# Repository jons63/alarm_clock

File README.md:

# Alarm clock with mp3 song support
This project spawned when my sister was looking to switch out her phone for an alarm clock.
She said that she easily wakes up in the morning so the normal alarm sounds are to harsh and
she would instead like to have nature sound like the ones usually available in wake up light
alarm clocks. I did a modest effort in trying to find what she wanted but when I finally
found an alarm clock that had nature sounds and no light the sound was horrible.
And now im here after thinking "how hard can it be to make an alarm clock that sounds decent?".

## The display
Any seven segment display with four digits should work for an alarm clock. I went with the largest available one.

Below is the wiring for the display + one button for incrementing the value shown.

## Display with shift register
A seven segment display require a lot of pins to operate, twelve for a display with four digits. To get around this I use a shift register to only use seven pins on the arduino instead of twelve.

But even when using a shift register the amount of digital pins on one Arduino Uno is not enough when adding the MP3 player and buttons. Also, when adding logic to handle button presses and the alarm functionality the update frequence of the display gets low enough for it to be visibly flickering. To combat this I will add another Arduino Uno that will only refresh the display and the second arduino will handle the logic. They will use i2c communication to change what time should be displayed and other functoin that might be needed.

## Dual Arduino Uno with i2c communication. 
i2c is an easy communication interface with good Arduino support from the Wire library. I copied a simple example of i2c communication between two Arduinos to test it out.

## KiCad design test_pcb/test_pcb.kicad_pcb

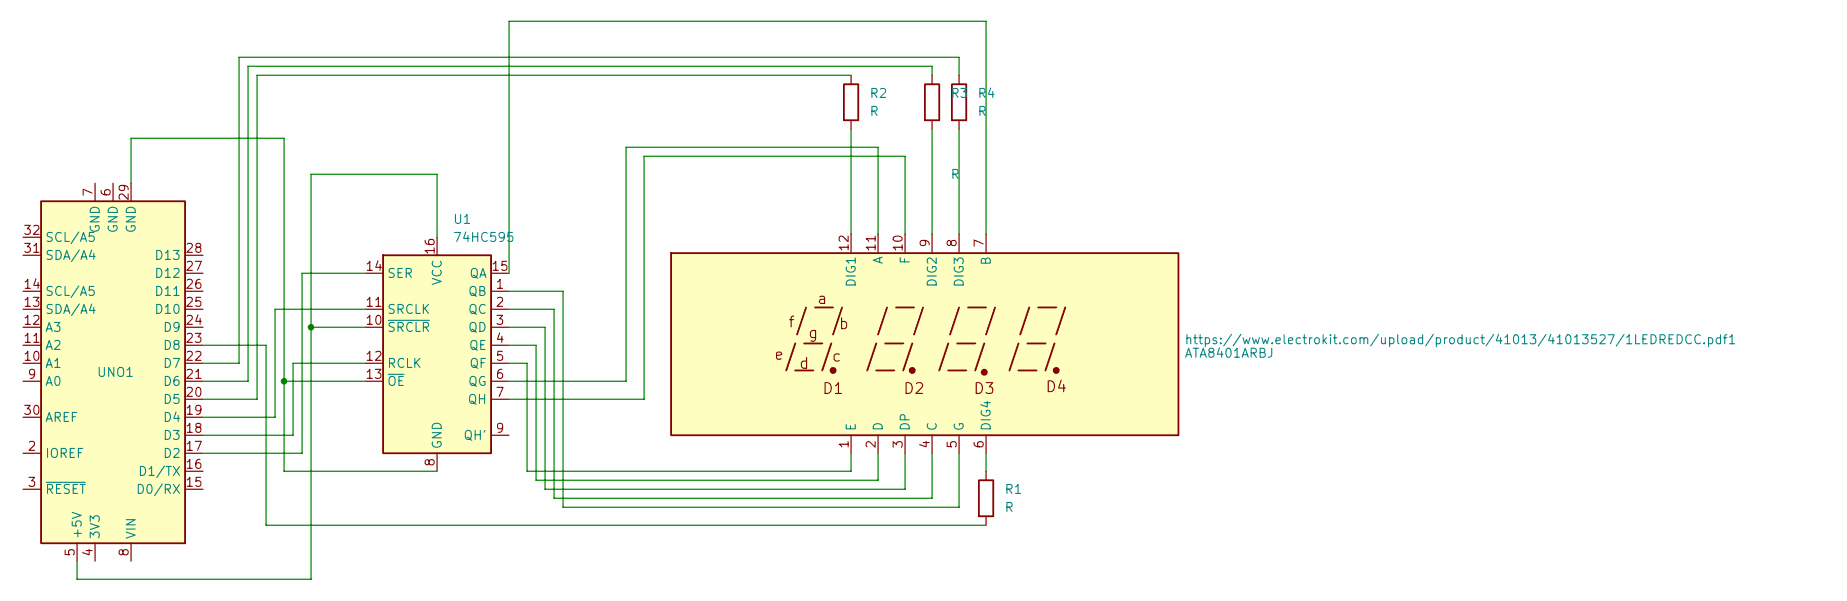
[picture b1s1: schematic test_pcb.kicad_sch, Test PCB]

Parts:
R1, R2, R3, R4: R; R_Axial_DIN0207_L6.3mm_D2.5mm_P10.16mm_Horizontal
U1: 74HC595; DIP-16_W7.62mm_Socket
UNO1: Arduino UNO R3 Outline
https://www.electrokit.com/upload/product/41013/41013527/1LEDREDCC.pdf1: ATA8401ARBJ

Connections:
unnamed: U1.8 (GND), U1.13 (~OE), UNO1.29 (GND)
unnamed: U1.15 (QA), https://www.electrokit.com/upload/produ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.7 (B)
unnamed: U1.1 (QB), https://www.electrokit.com/upload/produ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.5 (G)
unnamed: U1.2 (QC), https://www.electrokit.com/upload/produ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.4 (C)
unnamed: U1.3 (QD), https://www.electrokit.com/upload/produ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.3 (DP)
unnamed: U1.4 (QE), https://www.electrokit.com/upload/produ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.2 (D)
unnamed: U1.5 (QF), https://www.electrokit.com/upload/produ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.1 (E)
unnamed: U1.6 (QG), https://www.electrokit.com/upload/produ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.11 (A)
unnamed: U1.7 (QH), https://www.electrokit.com/upload/produ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.10 (F)
unnamed: U1.12 (RCLK), UNO1.18 (D3)
unnamed: U1.14 (SER), UNO1.17 (D2)
unnamed: U1.11 (SRCLK), UNO1.19 (D4)
unnamed: U1.10 (~SRCLR), U1.16 (VCC), UNO1.5 (+5V)
unnamed: R2.1, UNO1.20 (D5)
unnamed: R3.1, UNO1.21 (D6)
unnamed: R4.1, UNO1.22 (D7)
unnamed: R1.2, UNO1.23 (D8)
unnamed: R2.2, https://www.electrokit.com/upload/produ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.12 (DIG1)
unnamed: R3.2, https://www.electrokit.com/upload/produ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.9 (DIG2)
unnamed: R4.2, https://www.electrokit.com/upload/produ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.8 (DIG3)
unnamed: R1.1, https://www.electrokit.com/upload/produ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.6 (DIG4)

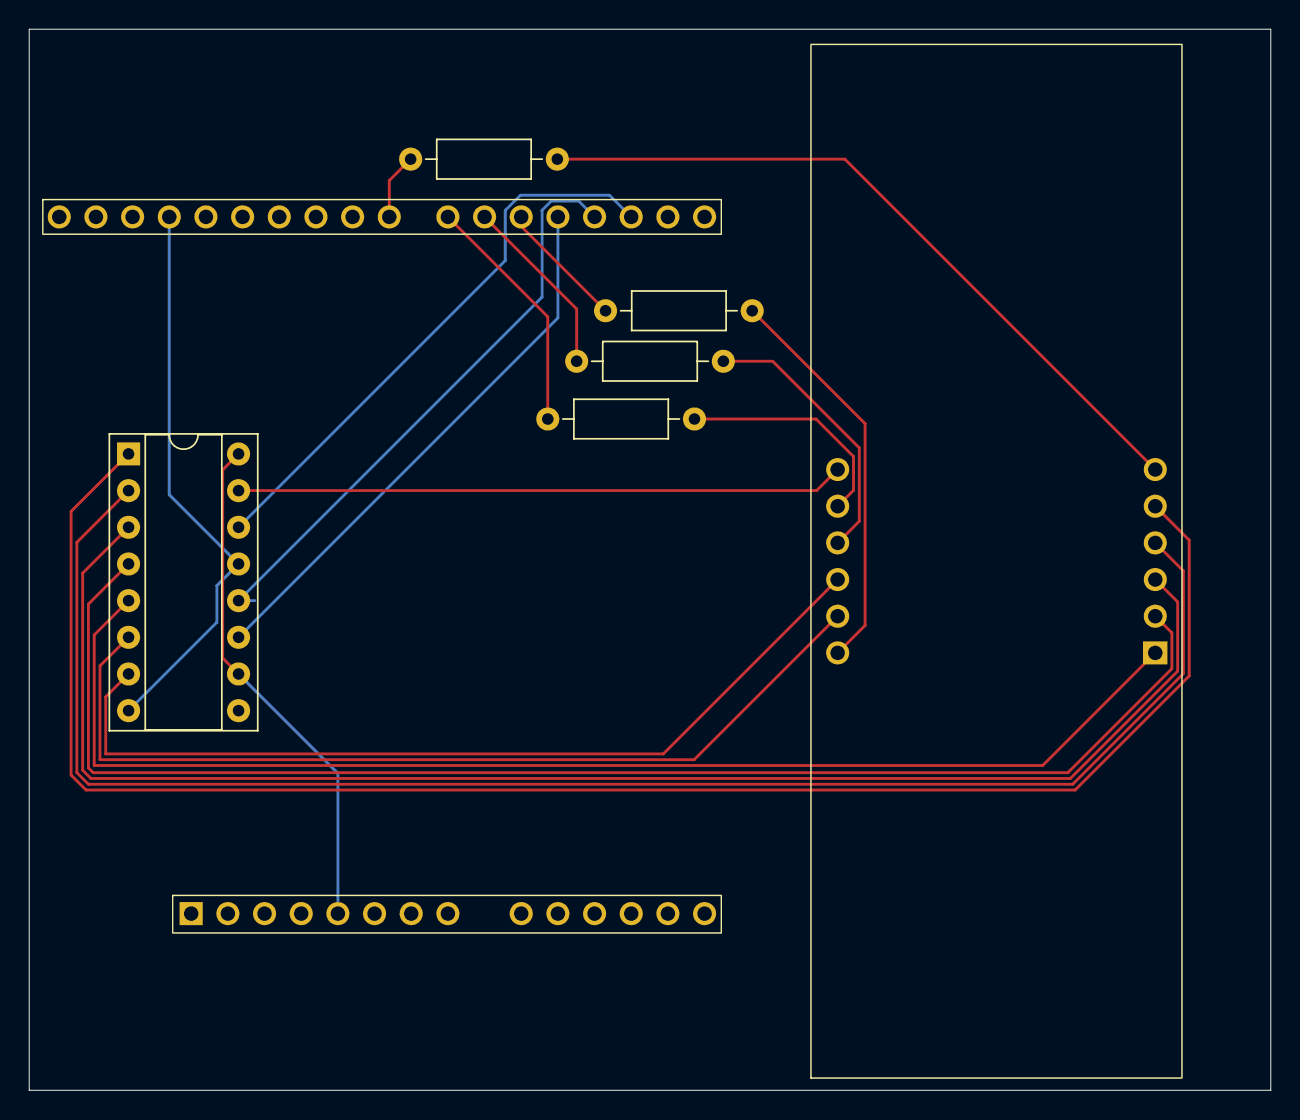
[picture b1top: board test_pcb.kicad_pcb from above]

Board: 2 copper layers, 86.0 x 73.5 mm, 7 parts (0 on the bottom side), 21 nets.

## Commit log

2024-04-01 Use shift register to reduce number of arduino pins used to drive the display.
2024-11-17 Add i2c example
2024-11-21 Adds example of reading/writing time beween 2 arduinos
2024-11-24 Adds posibility to increment displayed time
2024-11-24 Adds functionality to change display brightness
2024-11-25 Adds alarm functionality
2024-11-26 Clock plays music when alarm is active
